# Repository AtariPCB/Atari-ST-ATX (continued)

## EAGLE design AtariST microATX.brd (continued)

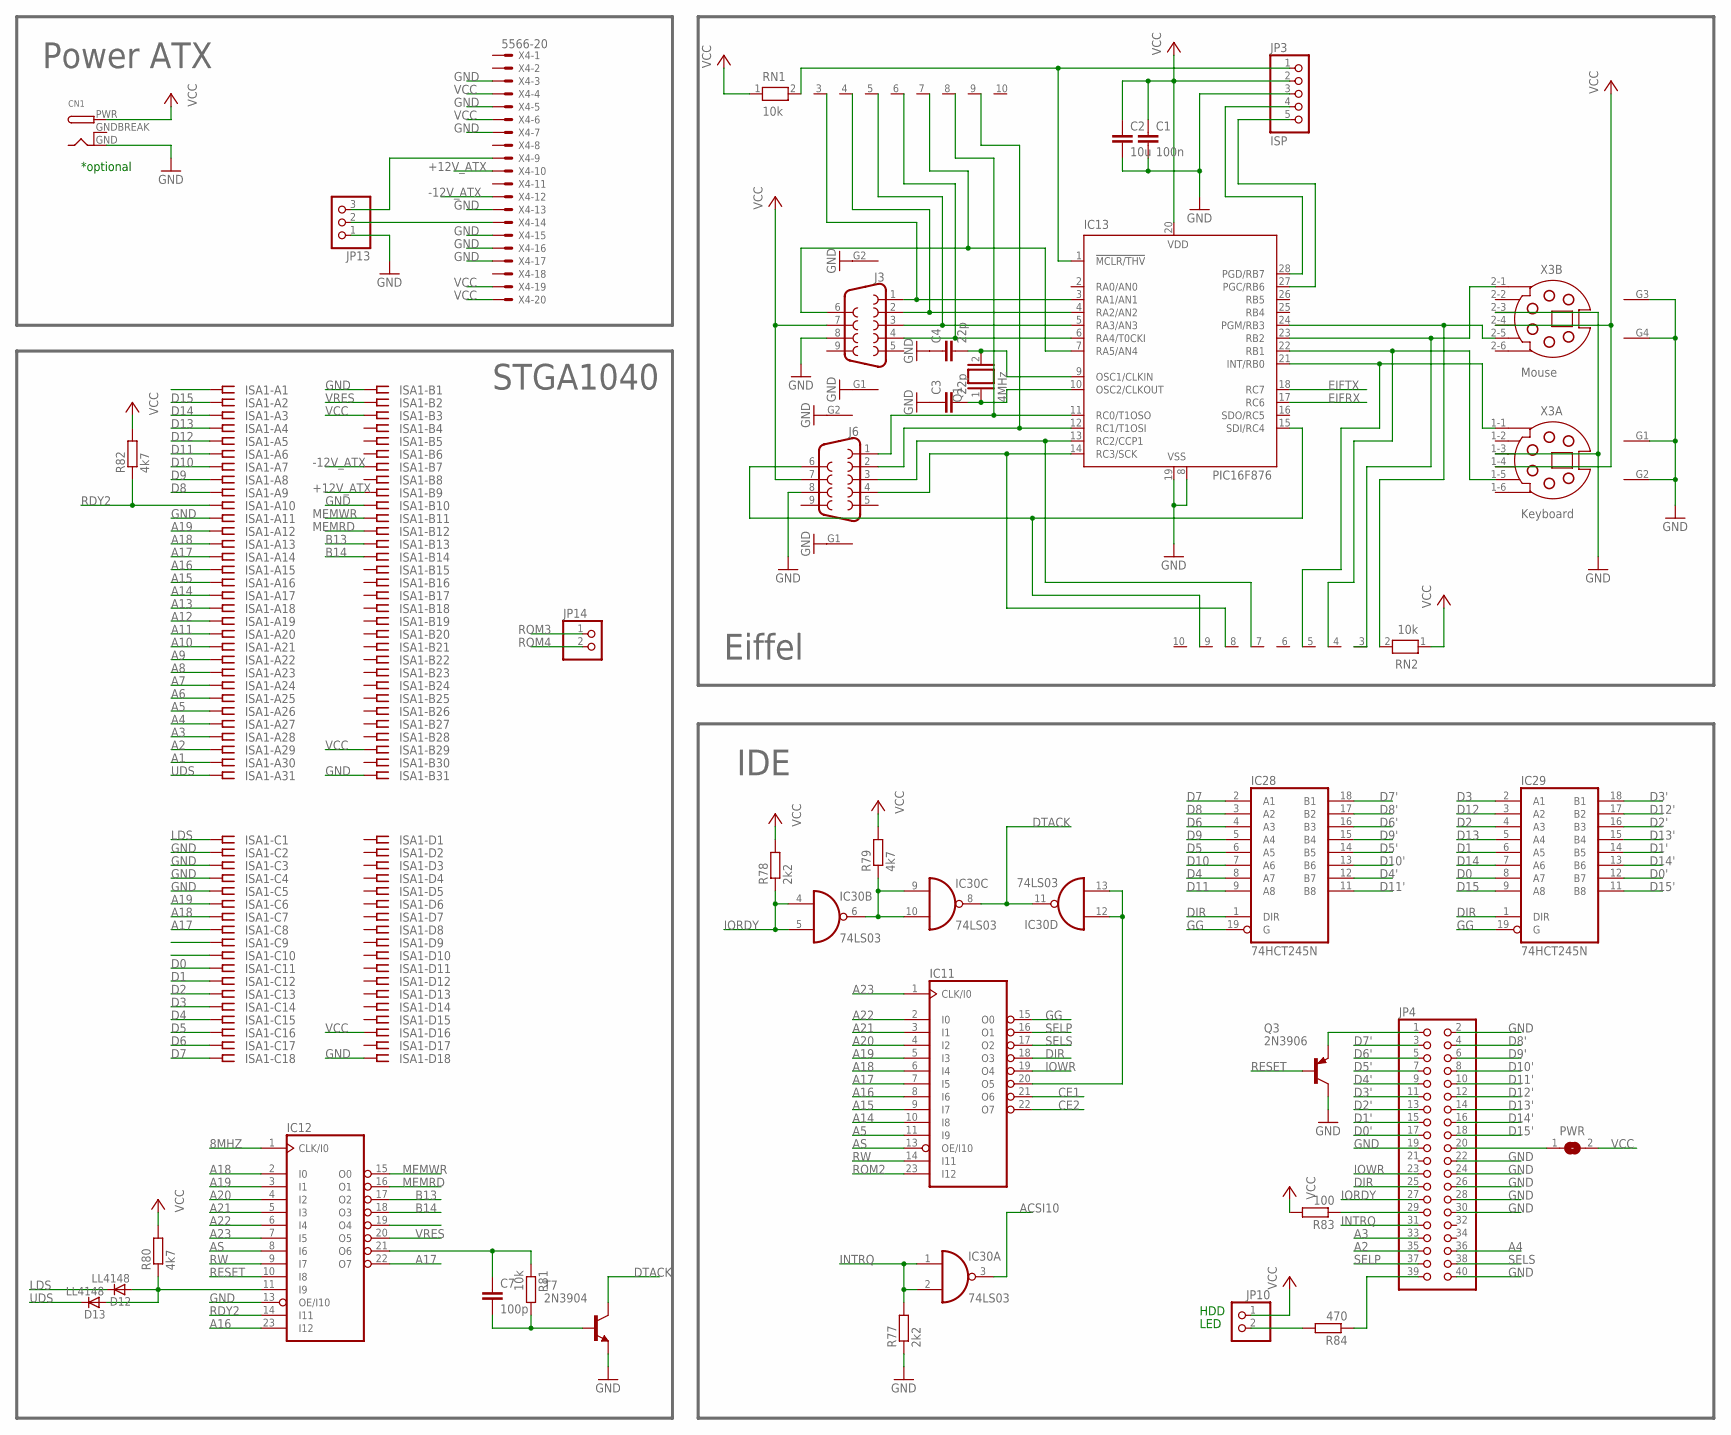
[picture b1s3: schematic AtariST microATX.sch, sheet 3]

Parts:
C1: 100n; C0805
C2: 10u; C1206
C3, C4: 22p; C0805
C7: 100p; C0805
CN1: DCBARRELPTH; DCJACK_2MM_PTH
D12, D13: LL4148; SOD80_DO213AA_MINIMELF
IC11, IC12: 20V8; DIL24-3
IC13: PIC16F876; DIL28-3
IC28, IC29: 74HCT245N; DIL20
IC30: 74LS03; SO14
ISA1: ISA-SLOT; ISA-16
J3, J6: DB9MALE; DB9_MALE
JP3: ISP; 1X05
JP4: PINHD-2X20; 2X20
JP10, JP14: PINHD-1X2; 1X02
JP13: PINHD-1X3; 1X03
PWR: SJ
Q1: 4MHz; QS
Q3: 2N3906; TO92
R77, R78: 2k2; R0805
R79, R80, R82: 4k7; R0805
R81: 10k; R0805
R83: 100; R0805
R84: 470; R0805
RN1, RN2: 10k; RN-10
T7: 2N3904; TO92
X3: MDSSV-BD06; SSV-BD06
X4: 5566-20

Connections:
8MHZ: IC12.1 (CLK/I0); also elsewhere on the board
+12V_ATX: ISA1.B9, X4.10
-12V_ATX: ISA1.B7, X4.12
A1: ISA1.A30; also elsewhere on the board
A2: ISA1.A29, JP4.35; also elsewhere on the board
A3: ISA1.A28, JP4.33; also elsewhere on the board
A4: ISA1.A27, JP4.36; also elsewhere on the board
A5: IC11.11 (I9), ISA1.A26; also elsewhere on the board
A6: ISA1.A25; also elsewhere on the board
A7: ISA1.A24; also elsewhere on the board
A8: ISA1.A23; also elsewhere on the board
A9: ISA1.A22; also elsewhere on the board
A10: ISA1.A21; also elsewhere on the board
A11: ISA1.A20; also elsewhere on the board
A12: ISA1.A19; also elsewhere on the board
A13: ISA1.A18; also elsewhere on the board
A14: IC11.10 (I8), ISA1.A17; also elsewhere on the board
A15: IC11.9 (I7), ISA1.A16; also elsewhere on the board
A16: IC11.8 (I6), IC12.23 (I12), ISA1.A15; also elsewhere on the board
A17: IC11.7 (I5), IC12.22 (O7), ISA1.A14, ISA1.C8; also elsewhere on the board
A18: IC11.6 (I4), IC12.2 (I0), ISA1.A13, ISA1.C7; also elsewhere on the board
A19: IC11.5 (I3), IC12.3 (I1), ISA1.A12, ISA1.C6; also elsewhere on the board
A20: IC11.4 (I2), IC12.4 (I2); also elsewhere on the board
A21: IC11.3 (I1), IC12.5 (I3); also elsewhere on the board
A22: IC11.2 (I0), IC12.6 (I4); also elsewhere on the board
A23: IC11.1 (CLK/I0), IC12.7 (I5); also elsewhere on the board
ACSI10: IC30.3 (O); also elsewhere on the board
AS: IC11.13 (OE/I10), IC12.8 (I6); also elsewhere on the board
B13: IC12.17 (O2), ISA1.B13
B14: IC12.18 (O3), ISA1.B14
CE1: IC11.21 (O6); also elsewhere on the board
CE2: IC11.22 (O7); also elsewhere on the board
D0: IC29.8 (A7), ISA1.C11; also elsewhere on the board
D0': IC29.12 (B7), JP4.17
D1: IC29.6 (A5), ISA1.C12; also elsewhere on the board
D1': IC29.14 (B5), JP4.15
D2: IC29.4 (A3), ISA1.C13; also elsewhere on the board
D2': IC29.16 (B3), JP4.13
D3: IC29.2 (A1), ISA1.C14; also elsewhere on the board
D3': IC29.18 (B1), JP4.11
D4: IC28.8 (A7), ISA1.C15; also elsewhere on the board
D4': IC28.12 (B7), JP4.9
D5: IC28.6 (A5), ISA1.C16; also elsewhere on the board
D5': IC28.14 (B5), JP4.7
D6: IC28.4 (A3), ISA1.C17; also elsewhere on the board
D6': IC28.16 (B3), JP4.5
D7: IC28.2 (A1), ISA1.C18; also elsewhere on the board
D7': IC28.18 (B1), JP4.3
D8: IC28.3 (A2), ISA1.A9; also elsewhere on the board
D8': IC28.17 (B2), JP4.4
D9: IC28.5 (A4), ISA1.A8; also elsewhere on the board
D9': IC28.15 (B4), JP4.6
D10: IC28.7 (A6), ISA1.A7; also elsewhere on the board
D10': IC28.13 (B6), JP4.8
D11: IC28.9 (A8), ISA1.A6; also elsewhere on the board
D11': IC28.11 (B8), JP4.10
D12: IC29.3 (A2), ISA1.A5; also elsewhere on the board
D12': IC29.17 (B2), JP4.12
D13: IC29.5 (A4), ISA1.A4; also elsewhere on the board
D13': IC29.15 (B4), JP4.14
D14: IC29.7 (A6), ISA1.A3; also elsewhere on the board
D14': IC29.13 (B6), JP4.16
D15: IC29.9 (A8), ISA1.A2; also elsewhere on the board
D15': IC29.11 (B8), JP4.18
DIR: IC11.18 (O3), IC28.1 (DIR), IC29.1 (DIR), JP4.25
DTACK: IC30.8 (O), IC30.11 (O), T7.1 (C); also elsewhere on the board
EIFRX: IC13.17 (RC6); also elsewhere on the board
EIFTX: IC13.18 (RC7); also elsewhere on the board
GG: IC11.15 (O0), IC28.19 (G), IC29.19 (G)
GND: C1.2, C2.2, C3.1, C4.1, CN1.GND, IC11.12 (GND), IC12.12 (GND), IC12.13 (OE/I10), IC13.8 (VSS), IC13.19 (VSS), IC28.10 (GND), IC29.10 (GND), IC30.7 (GND), ISA1.A11, ISA1.B1, ISA1.B10, ISA1.B31, ISA1.C2, ISA1.C3, ISA1.C4, ISA1.C5, ISA1.D18, J3.8, J3.G1 (10), J3.G2 (11), J6.8, J6.G1 (10), J6.G2 (11), JP3.3, JP4.2, JP4.19, JP4.22, JP4.24, JP4.26, JP4.28, JP4.30, JP4.40, JP13.1, Q3.1 (C), R77.1, T7.3 (E), X3.1-3 (3), X3.2-3 (3), X3.G1, X3.G2, X3.G3, X3.G4, X4.3, X4.5, X4.7, X4.13, X4.15, X4.16, X4.17; also elsewhere on the board
GNDBREAK: CN1.GNDBREAK
INTRQ: IC30.1 (I0), IC30.2 (I1), JP4.31, R77.2
IORDY: IC30.4 (I0), IC30.5 (I1), JP4.27, R78.1
IOWR: IC11.19 (O4), JP4.23
LDS: D12.C, ISA1.C1; also elsewhere on the board
MEMRD: IC12.16 (O1), ISA1.B12
MEMWR: IC12.15 (O0), ISA1.B11
unnamed: IC13.1 (!MCLR/THV), JP3.1, RN1.2
unnamed: C3.2, IC13.10 (OSC2/CLKOUT), Q1.1
unnamed: IC13.28 (PGD/RB7), JP3.4
unnamed: IC13.27 (PGC/RB6), JP3.5
unnamed: C4.2, IC13.9 (OSC1/CLKIN), Q1.2
unnamed: IC13.3 (RA1/AN1), J3.1, RN1.3
unnamed: IC13.4 (RA2/AN2), J3.2, RN1.4
unnamed: IC13.5 (RA3/AN3), J3.3, RN1.5
unnamed: IC13.24 (PGM/RB3), RN2.2, X3.2-5 (5)
unnamed: IC13.22 (RB1), RN2.4, X3.1-5 (5)
unnamed: IC13.11 (RC0/T1OSO), J6.1, RN1.8
unnamed: IC13.12 (RC1/T1OSI), J6.2, RN1.9
unnamed: IC13.13 (RC2/CCP1), J6.3, RN2.7
unnamed: IC13.14 (RC3/SCK), J6.4, RN2.8
unnamed: IC13.15 (SDI/RC4), J6.6, RN2.9
unnamed: IC13.23 (RB2), RN2.3, X3.2-1 (1)
unnamed: IC13.21 (INT/RB0), RN2.5, X3.1-1 (1)
unnamed: IC13.7 (RA5/AN4), J3.6, RN1.7
unnamed: IC13.6 (RA4/T0CKI), J3.4, RN1.6
unnamed: IC30.6 (O), IC30.9 (I0), IC30.10 (I1), R79.1
unnamed: JP4.39, R84.1
unnamed: IC11.20 (O5), IC30.12 (I0), IC30.13 (I1)
unnamed: JP4.29, R83.1
unnamed: JP4.20, PWR.1
unnamed: JP4.1, Q3.3 (E)
unnamed: D12.A, D13.A, IC12.11 (I9), R80.1
unnamed: C7.2, R81.2, T7.2 (B)
unnamed: JP10.2, R84.2
unnamed: JP13.2, X4.14
unnamed: JP13.3, X4.9
unnamed: C7.1, IC12.21 (O6), R81.1
RDY2: IC12.14 (I11), ISA1.A10, R82.1
RESET: IC12.10 (I8), Q3.2 (B); also elsewhere on the board
ROM2: IC11.23 (I12); also elsewhere on the board
ROM3: JP14.1; also elsewhere on the board
ROM4: JP14.2; also elsewhere on the board
RW: IC11.14 (I11), IC12.9 (I7); also elsewhere on the board
SELP: IC11.16 (O1), JP4.37
SELS: IC11.17 (O2), JP4.38
UDS: D13.C, ISA1.A31; also elsewhere on the board
VCC: C1.1, C2.1, CN1.PWR, IC11.24 (VCC), IC12.24 (VCC), IC13.20 (VDD), IC28.20 (VCC), IC29.20 (VCC), IC30.14 (VCC), ISA1.B3, ISA1.B29, ISA1.D16, J3.7, J6.7, JP3.2, JP10.1, PWR.2, R78.2, R79.2, R80.2, R82.2, R83.2, RN1.1, RN2.1, X3.1-4 (4), X3.2-4 (4), X4.4, X4.6, X4.19, X4.20; also elsewhere on the board
VRES: IC12.20 (O5), ISA1.B2

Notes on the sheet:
Keyboard
Mouse
Eiffel
IDE
Power ATX
STGA1040
HDD
LED
*optional

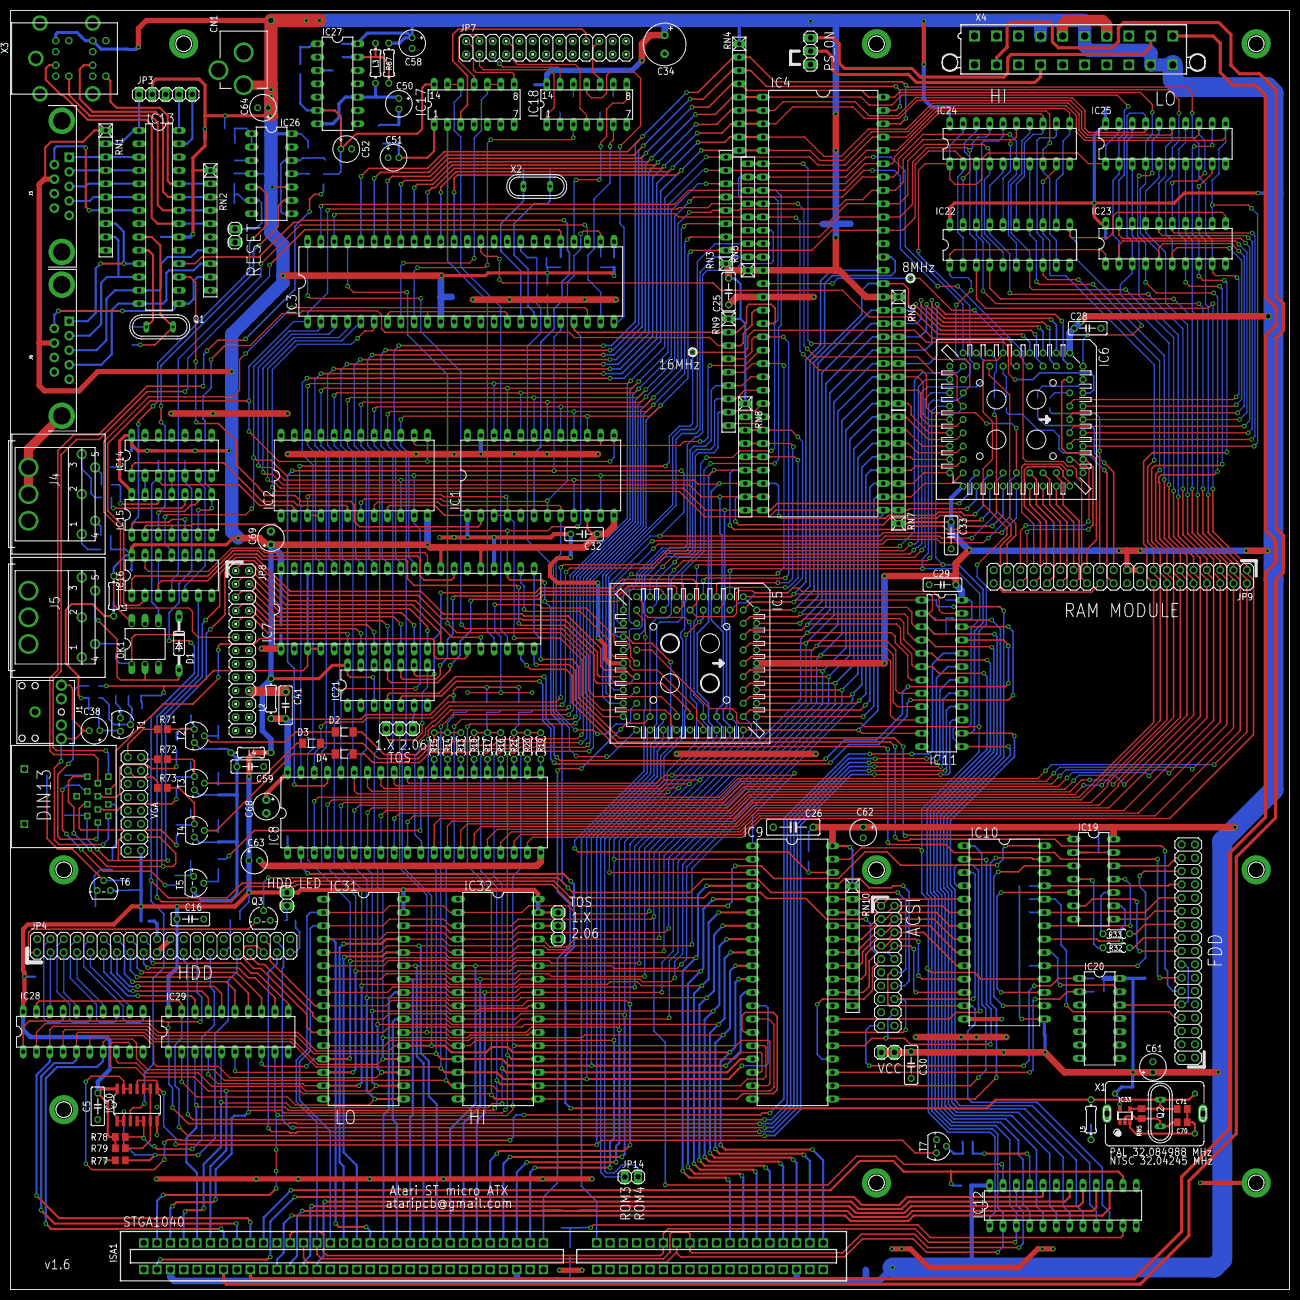
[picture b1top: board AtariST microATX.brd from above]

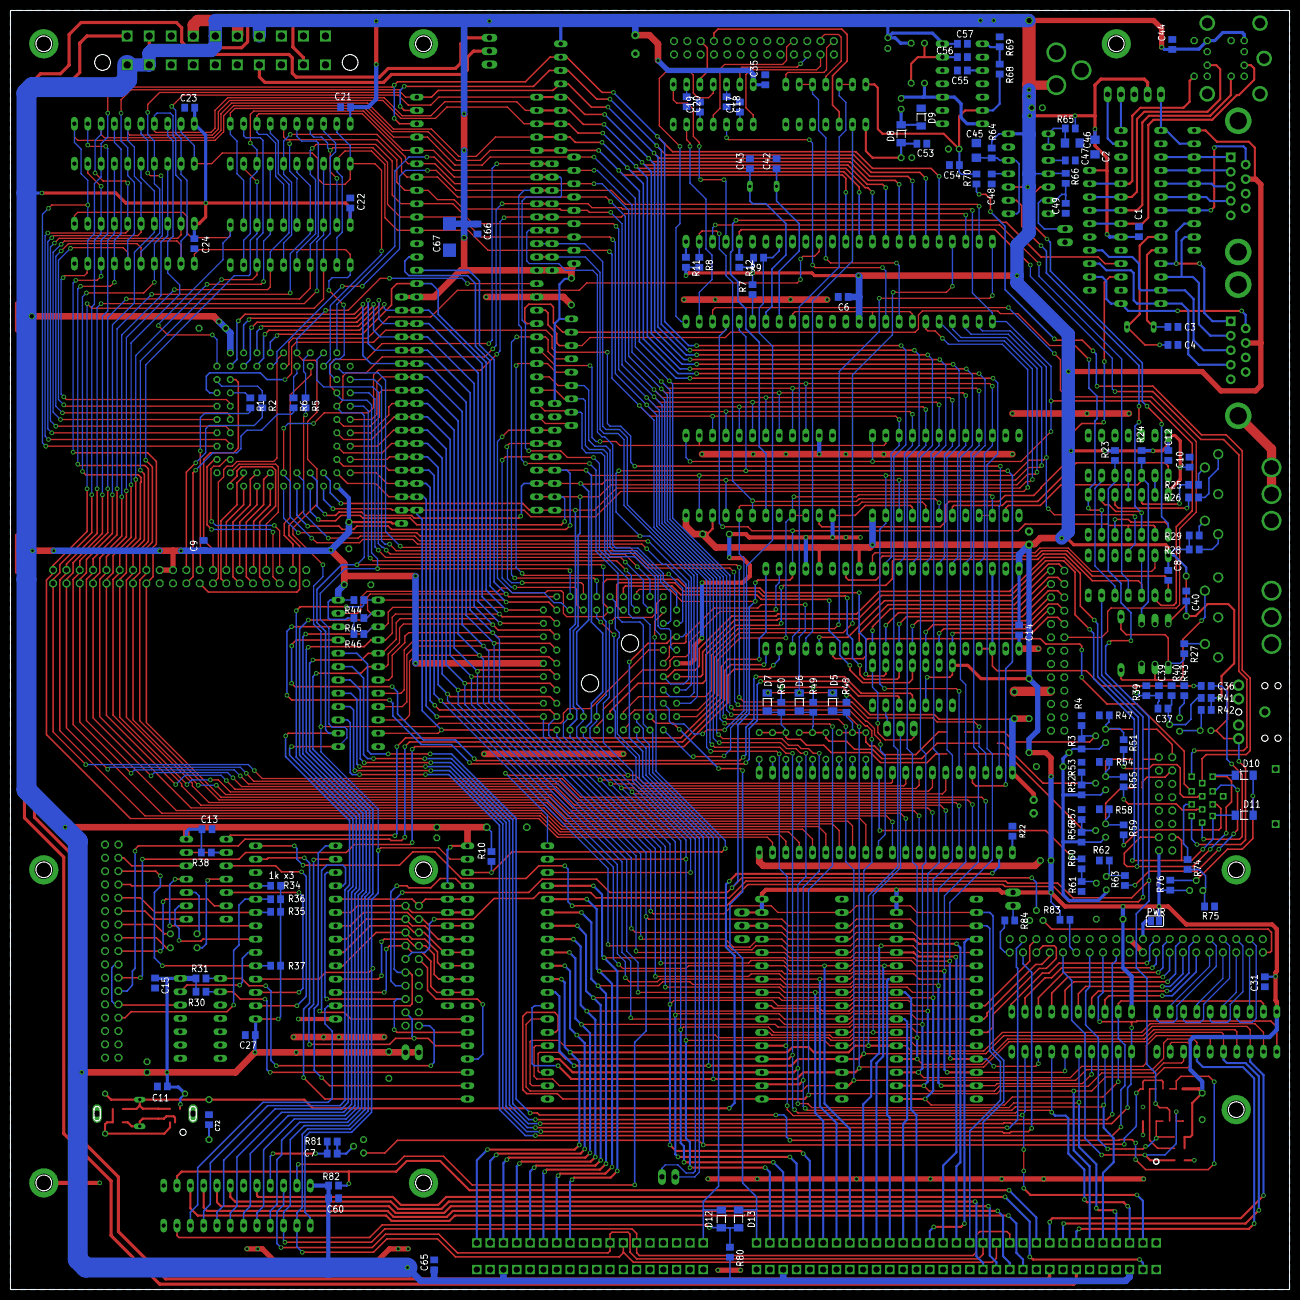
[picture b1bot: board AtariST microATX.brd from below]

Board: 2 copper layers, 243.8 x 243.8 mm, 257 parts (123 on the bottom side), 348 nets.

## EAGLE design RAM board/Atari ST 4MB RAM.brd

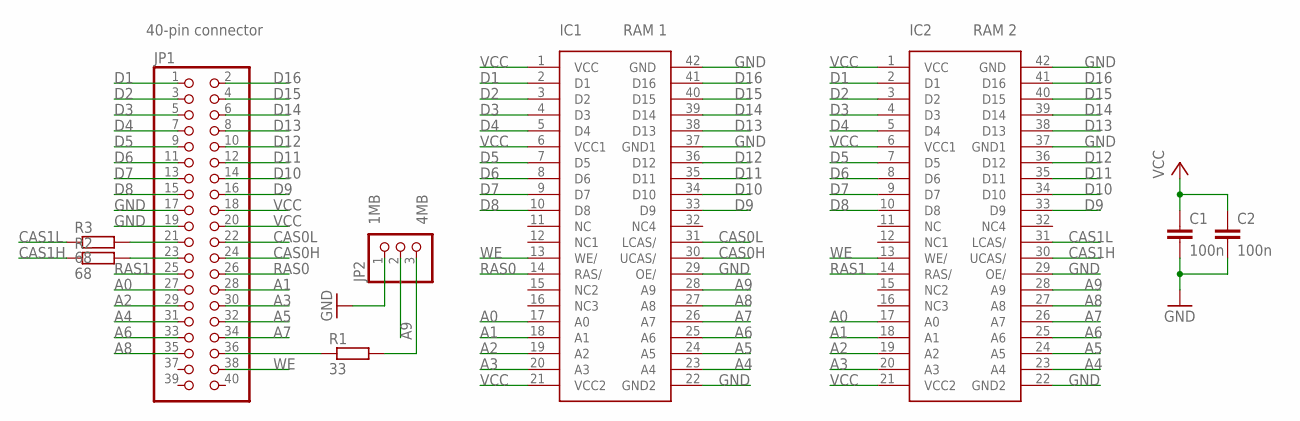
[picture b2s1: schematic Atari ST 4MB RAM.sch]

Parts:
C1, C2: 100n; C0805
IC1, IC2: DRAMSOJ40A; SOJ40
JP1: PINHD-2X20; 2X20
JP2: PINHD-1X3; 1X03
R1: 33; R0805
R2, R3: 68; R0805

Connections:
A0: IC1.17 (A0), IC2.17 (A0), JP1.27
A1: IC1.18 (A1), IC2.18 (A1), JP1.28
A2: IC1.19 (A2), IC2.19 (A2), JP1.29
A3: IC1.20 (A3), IC2.20 (A3), JP1.30
A4: IC1.23 (A4), IC2.23 (A4), JP1.31
A5: IC1.24 (A5), IC2.24 (A5), JP1.32
A6: IC1.25 (A6), IC2.25 (A6), JP1.33
A7: IC1.26 (A7), IC2.26 (A7), JP1.34
A8: IC1.27 (A8), IC2.27 (A8), JP1.35
A9: IC1.28 (A9), IC2.28 (A9), JP2.2
CAS0H: IC1.30 (UCAS/), JP1.24
CAS0L: IC1.31 (LCAS/), JP1.22
CAS1H: IC2.30 (UCAS/), R2.1
CAS1L: IC2.31 (LCAS/), R3.1
D1: IC1.2 (D1), IC2.2 (D1), JP1.1
D2: IC1.3 (D2), IC2.3 (D2), JP1.3
D3: IC1.4 (D3), IC2.4 (D3), JP1.5
D4: IC1.5 (D4), IC2.5 (D4), JP1.7
D5: IC1.7 (D5), IC2.7 (D5), JP1.9
D6: IC1.8 (D6), IC2.8 (D6), JP1.11
D7: IC1.9 (D7), IC2.9 (D7), JP1.13
D8: IC1.10 (D8), IC2.10 (D8), JP1.15
D9: IC1.33 (D9), IC2.33 (D9), JP1.16
D10: IC1.34 (D10), IC2.34 (D10), JP1.14
D11: IC1.35 (D11), IC2.35 (D11), JP1.12
D12: IC1.36 (D12), IC2.36 (D12), JP1.10
D13: IC1.38 (D13), IC2.38 (D13), JP1.8
D14: IC1.39 (D14), IC2.39 (D14), JP1.6
D15: IC1.40 (D15), IC2.40 (D15), JP1.4
D16: IC1.41 (D16), IC2.41 (D16), JP1.2
GND: C1.2, C2.2, IC1.22 (GND2), IC1.29 (OE/), IC1.37 (GND1), IC1.42 (GND), IC2.22 (GND2), IC2.29 (OE/), IC2.37 (GND1), IC2.42 (GND), JP1.17, JP1.19, JP2.1
unnamed: JP1.21, R3.2
unnamed: JP1.23, R2.2
unnamed: JP1.36, R1.1
unnamed: JP2.3, R1.2
RAS0: IC1.14 (RAS/), JP1.26
RAS1: IC2.14 (RAS/), JP1.25
VCC: C1.1, C2.1, IC1.1 (VCC), IC1.6 (VCC1), IC1.21 (VCC2), IC2.1 (VCC), IC2.6 (VCC1), IC2.21 (VCC2), JP1.18, JP1.20
WE: IC1.13 (WE/), IC2.13 (WE/), JP1.38

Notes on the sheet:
4MB
1MB
40-pin connector
RAM 1
RAM 2

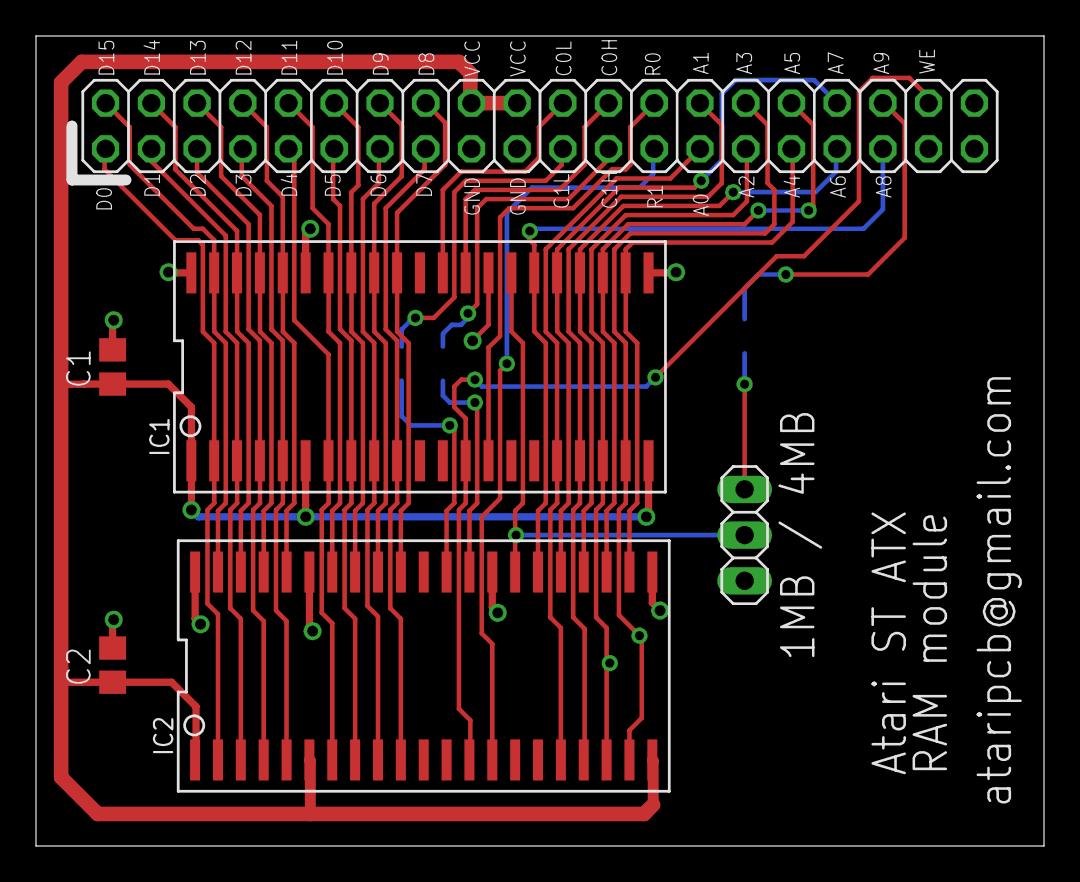
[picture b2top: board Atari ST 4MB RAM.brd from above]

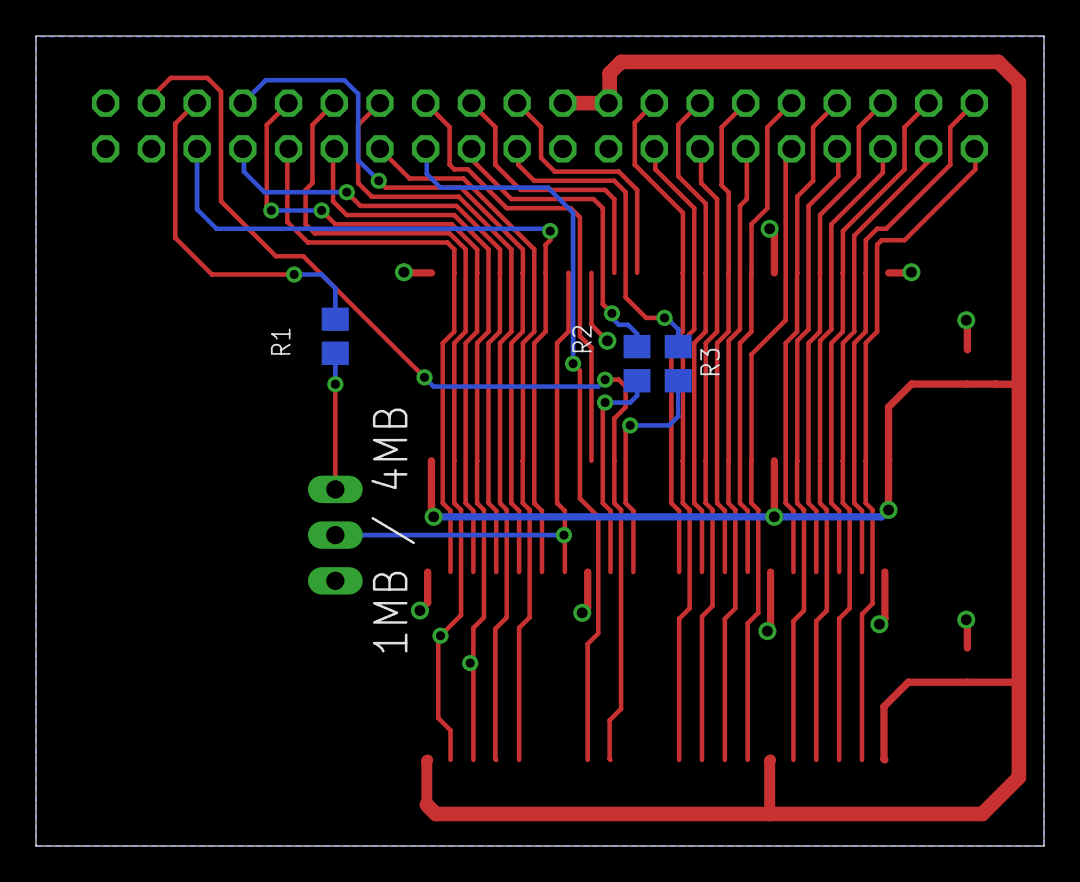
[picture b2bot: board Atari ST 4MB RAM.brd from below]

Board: 2 copper layers, 56.0 x 45.0 mm, 9 parts (3 on the bottom side), 39 nets.

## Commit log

2025-07-18 Create a
2025-07-22 Add files
